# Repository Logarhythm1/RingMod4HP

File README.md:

# RingMod4HP
CC-By-NC 4.0, 2024 (Non-commercial use permitted)

An AD633-based Ring Modulator in Eurorack format (4HP)

This is based on a design by Roman Sowa, who has kindly allowed me to share this implementation for anyone to build.

It's a great, clean-sounding ring modulator featuring the excellent AD633 IC.
The board is a pretty simple build, with mostly 0603 components. Two footprints are provided for the AD633 IC, and you should choose either DIP or soic package to place. No BOM is provided but it's pretty easy to see what's needed from the schematic. The specific hardware needed is:

- 3 Thonkiconn jacks
- 1 10k vertical 9mm pot
- 2 100k pots
- 2 micromini 3-way switches

Eagle 6 format schematic, board, and panel files are included.

Zip files containing the board and panel gerbers are also included.

Note: Images show the 1.0 version of the board and panel, which have a couple of errors that are corrected in the 1.1 versions presented here. Both were ordered from JLCPCB, with the panel as an "aluminum pcb." The panel came back with white paint and raw aluminum text, which is the inverse of what I expected but it works for me.

Version 1.0 board and panel:

Version 1.1 layout:

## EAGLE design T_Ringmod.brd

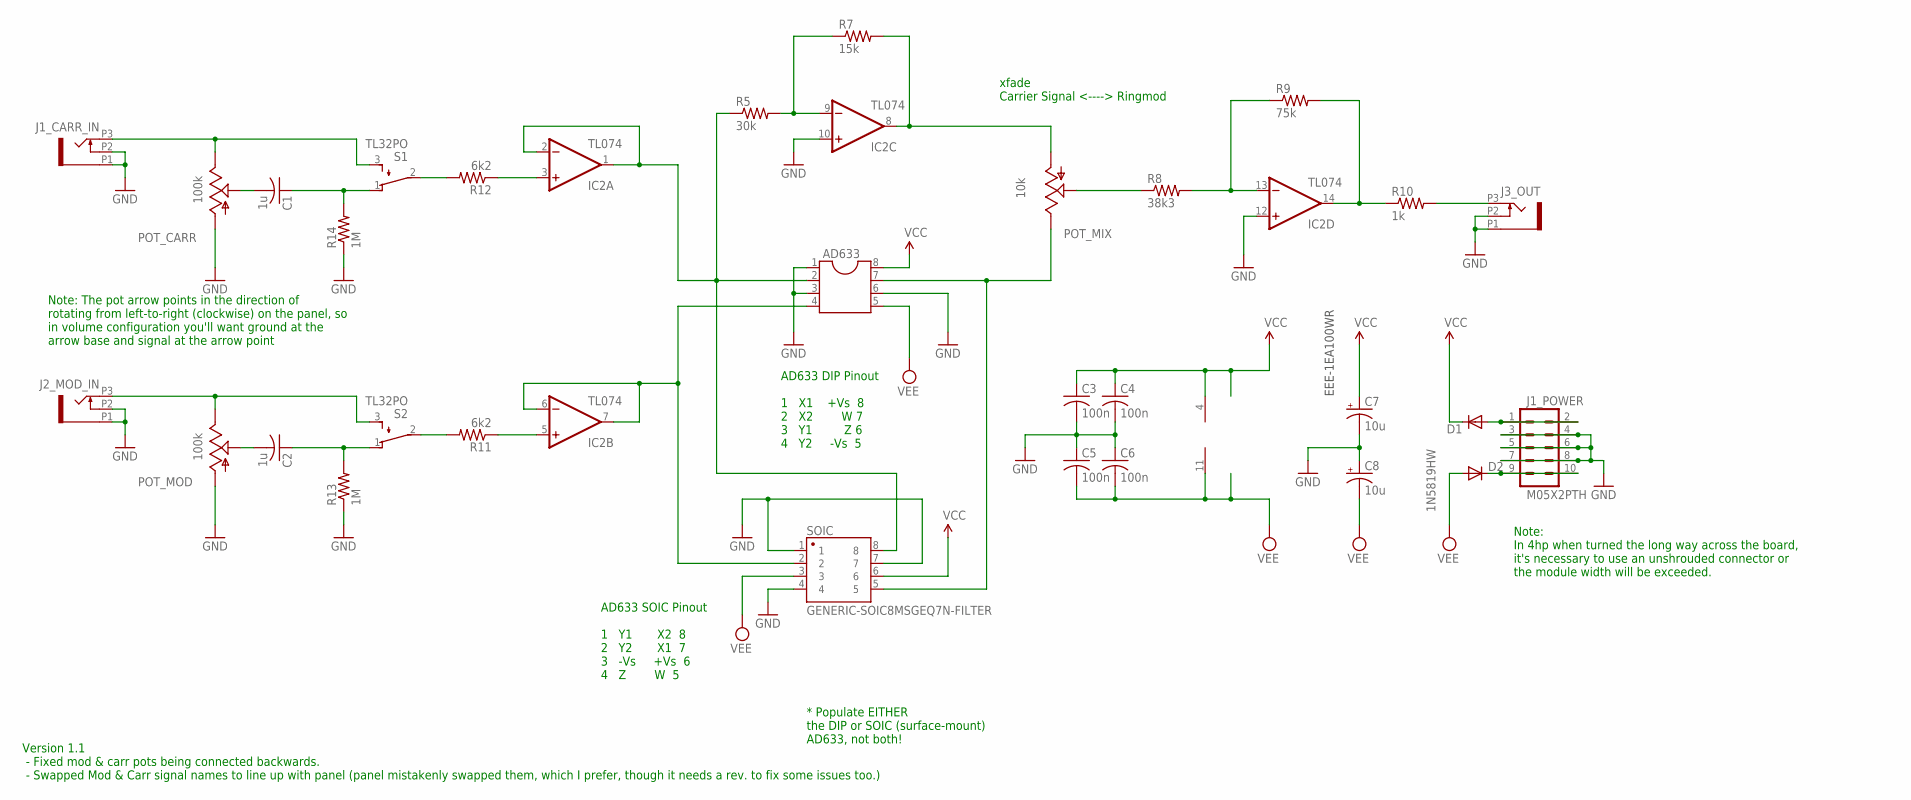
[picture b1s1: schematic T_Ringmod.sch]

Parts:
AD633: DIL8; DIL08
C1, C2: 1u; C0805
C3, C4, C5, C6: 100n; C0805
C7, C8: 10u; PANASONIC_A
D1, D2: 1N5819HW; SOD123
IC2: TL074; SO14
J1_CARR_IN, J2_MOD_IN, J3_OUT: PJ301_THONKICONN6; WQP_PJ_301M6
J1_POWER: M05X2PTH; AVR_ICSP
POT_CARR: 100k; ALPS_POT_VERTICAL_PS
POT_MIX: 10k; ALPS_POT_VERTICAL_PS
POT_MOD: 100k; ALPS_POT_VERTICAL_PS
R5: 30k; R0805
R7: 15k; R0805
R8: 38k3; R0805
R9: 75k; R0805
R10: 1k; R0805
R11, R12: 6k2; R0805
R13, R14: 1M; R0805
S1, S2: TL32PO; TL3XPO
SOIC: GENERIC-SOIC8MSGEQ7N-FILTER; SO08

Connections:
GND: AD633.1, AD633.3, AD633.6, C3.2, C4.2, C5.1, C6.1, C7.-, C8.+, IC2.10 (+IN), IC2.12 (+IN), J1_CARR_IN.P1 (1), J1_CARR_IN.P2 (2), J1_POWER.3, J1_POWER.4, J1_POWER.5, J1_POWER.6, J1_POWER.7, J1_POWER.8, J2_MOD_IN.P1 (1), J2_MOD_IN.P2 (2), J3_OUT.P1 (1), J3_OUT.P2 (2), POT_CARR.P$3 (A), POT_MOD.P$3 (A), R13.1, R14.1, SOIC.1, SOIC.4, SOIC.7
unnamed: C2.2, POT_MOD.P$2 (S)
unnamed: C1.2, POT_CARR.P$2 (S)
unnamed: C1.1, R14.2, S1.1 (O)
unnamed: R12.2, S1.2
unnamed: IC2.3 (+IN), R12.1
unnamed: D1.A, J1_POWER.1, J1_POWER.2
unnamed: AD633.2, IC2.1 (OUT), IC2.2 (-IN), R5.1, SOIC.8
unnamed: IC2.5 (+IN), R11.1
unnamed: R11.2, S2.2
unnamed: C2.1, R13.2, S2.1 (O)
unnamed: AD633.4, IC2.6 (-IN), IC2.7 (OUT), SOIC.2
unnamed: IC2.9 (-IN), R5.2, R7.1
unnamed: IC2.8 (OUT), POT_MIX.P$3 (A), R7.2
unnamed: AD633.7, POT_MIX.P$1 (E), SOIC.5
unnamed: J2_MOD_IN.P3 (3), POT_MOD.P$1 (E), S2.3 (S)
unnamed: J1_CARR_IN.P3 (3), POT_CARR.P$1 (E), S1.3 (S)
unnamed: POT_MIX.P$2 (S), R8.1
unnamed: IC2.13 (-IN), R8.2, R9.1
unnamed: D2.C, J1_POWER.9, J1_POWER.10
unnamed: IC2.14 (OUT), R9.2, R10.1
unnamed: J3_OUT.P3 (3), R10.2
VCC: AD633.8, C3.1, C4.1, C7.+, D1.C, IC2.4 (V+), SOIC.6
VEE: AD633.5, C5.2, C6.2, C8.-, D2.A, IC2.11 (V-), SOIC.3

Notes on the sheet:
EEE-1EA100WR
AD633 DIP Pinout 1 X1 +Vs 8 2 X2 W 7 3 Y1 Z 6 4 Y2 -Vs 5
xfade Carrier Signal <----> Ringmod
AD633 SOIC Pinout 1 Y1 X2 8 2 Y2 X1 7 3 -Vs +Vs 6 4 Z W 5
* Populate EITHER the DIP or SOIC (surface-mount) AD633, not both!
Version 1.1 - Fixed mod & carr pots being connected backwards. - Swapped Mod & Carr signal names to line up with panel (panel mistakenly swapped them, which I prefer, though it needs a rev. to fix some issues too.)
Note: The pot arrow points in the direction of rotating from left-to-right (clockwise) on the panel, so in volume configuration you'll want ground at the arrow base and signal at the arrow point
Note: In 4hp when turned the long way across the board, it's necessary to use an unshrouded connector or the module width will be exceeded.

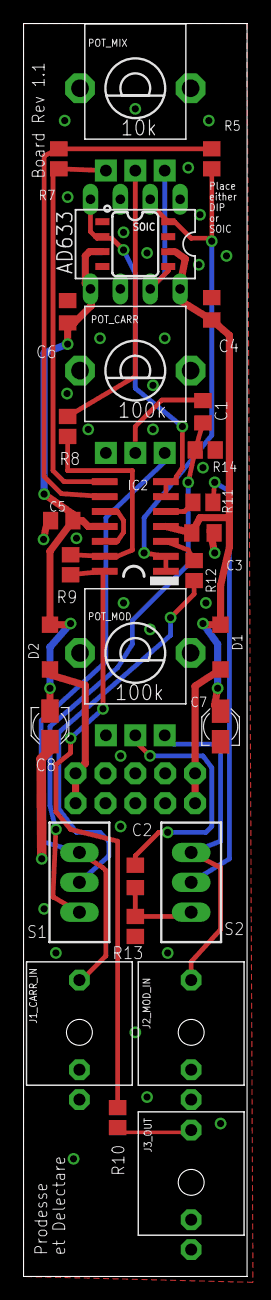
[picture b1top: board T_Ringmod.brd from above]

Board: 2 copper layers, 19.0 x 106.5 mm, 31 parts (1 on the bottom side), 24 nets.

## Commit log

2024-06-27 Rev 1.1 Eagle6 files and gerbers in zips
2024-06-27 Added image of eagle schematic

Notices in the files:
parts and their libraries:
SparkFun-Retired: Licensing: Creative Commons ShareAlike 4.0 International - https://creativecommons.org/licenses/by-sa/4.0
